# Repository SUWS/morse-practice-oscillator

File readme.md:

# Morse Code Practice oscillator

This contains the hardware and firmware designs for a morse code practice oscillator.

## Features

* 9v Battery or 12vDC powered
* Headphone or internal speaker output
* Adjustable Tone and Volume
* Support for paddle keys with variable speed and weight
* Capacitive iambic key unit included on PCB

## Sources and links

* Audio path based on designs by [Forrest Cook (WB0RIO)](http://www.solorb.com/elect/hamcirc/sidetone/)
* Capacitive Iambic key uses circuit from [John Parfrey (M0UKD)](https://m0ukd.com/homebrew/capacitive-cw-touch-key-circuits/)
* Project uses CC By icons from Dave Gandy (power icon (also remixed to make the dial and jack labels)) and Hanan (headphone icon)

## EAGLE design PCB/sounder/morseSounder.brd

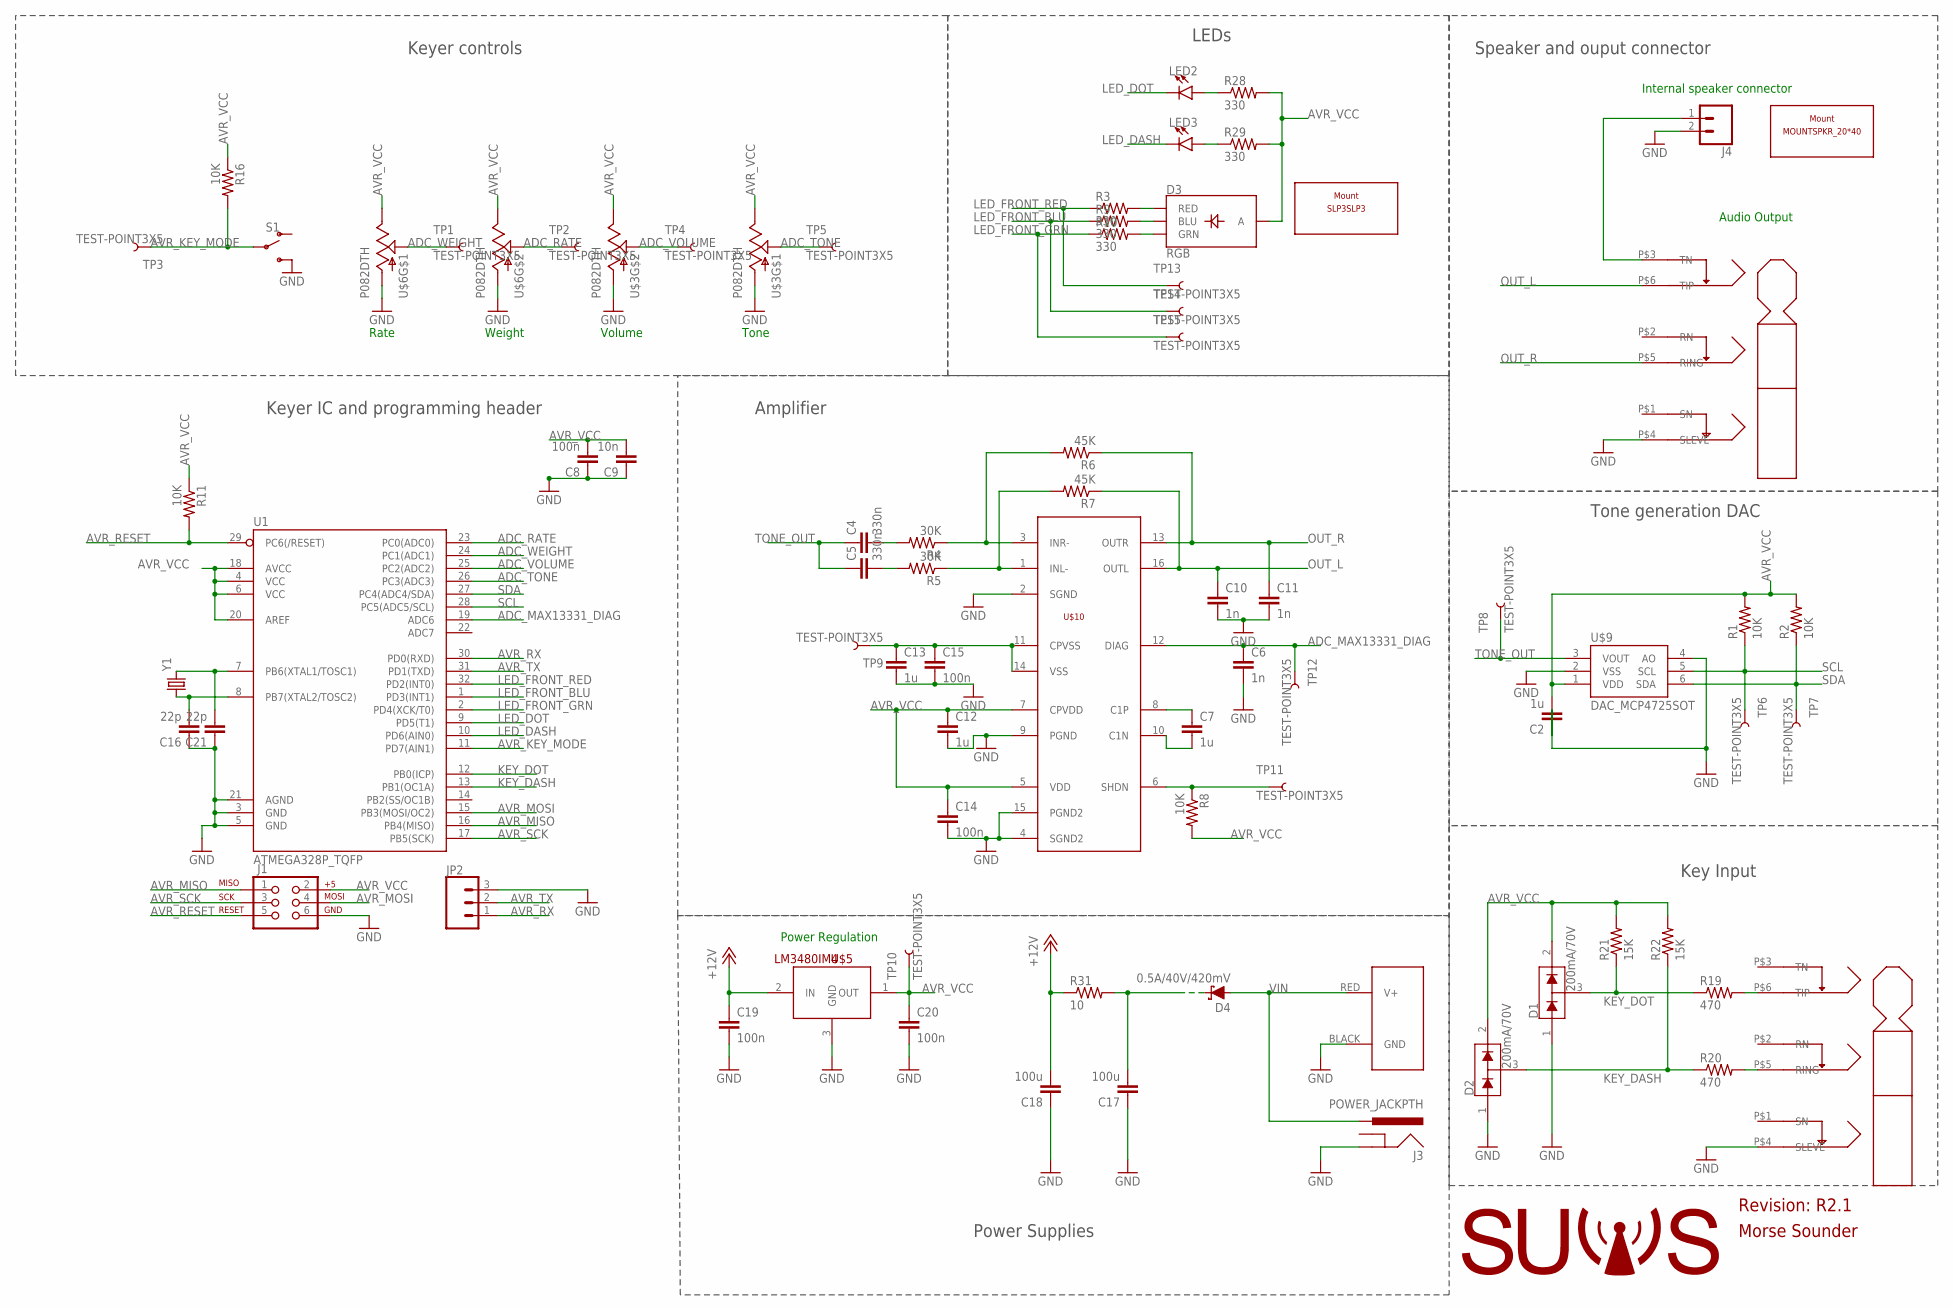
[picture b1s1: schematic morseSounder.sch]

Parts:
C2, C7, C12, C13: 1u; 0805
C4, C5: 330n; 0805
C6, C10, C11: 1n; 0805
C8, C14, C15, C19, C20: 100n; 0805
C9: 10n; 0805
C16, C21: 22p; 0805
C17, C18: 100u; 0805
D1, D2: 200mA/70V; SOT23-3
D3: RGB; P-LCC-4-3
D4: 0.5A/40V/420mV; SOD-323
J1: AVR_SPI_PRG_6PTH; 2X3
J2: POWERPOLE_POWER25A_HORIZONTAL_G2; POWERPOLE_PAIR_25A_HORIZ_G2
J3: POWER_JACKPTH; POWER_JACK_PTH
J4: CONN_02; 1X02
JP2: CONN_03; 1X03
LED2, LED3: LED-RED1206; LED-1206
R1, R2, R8, R11, R16: 10K; 0805
R3, R9, R10, R28, R29: 330; 0805
R4, R5: 30K; 0805
R6, R7: 45K; 0805
R19, R20: 470; 0805
R21, R22: 15K; 0805
R31: 10; 0805
S1: SWITCH-SPDTTE-1825232-1; TE-1825232-1
TP1, TP2, TP3, TP4, TP5, TP6, TP7, TP8, TP9, TP10, TP11, TP12, TP13, TP14, TP15: TEST-POINT3X5; PAD.03X.05
U1: ATMEGA328P_TQFP; TQFP32-08
U$1, U$2: NRJ6HH
U$3, U$6: P082DTH; P082D
U$4: MOUNTSPKR_20*40; SKR_MNT
U$5: LM3480IM4; SOT23-3
U$7: LOGO_SUWSLOGO_LARGE; LOGO_SUWS
U$8: SLP3SLP3; SLP-3
U$9: DAC_MCP4725SOT; SOT23-6
U$10: MAX13331; SSOP16
Y1: CRYSTALHC49UV; HC49U-V

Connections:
+12V: C18.2, C19.1, R31.1, U$5.2 (IN)
ADC_MAX13331_DIAG: C6.1, TP12.P$1, U1.19 (ADC6), U$10.12 (DIAG)
ADC_RATE: TP2.P$1, U1.23 (PC0(ADC0)), U$6.R2 (S)
ADC_TONE: TP5.P$1, U1.26 (PC3(ADC3)), U$3.F2 (S)
ADC_VOLUME: TP4.P$1, U1.25 (PC2(ADC2)), U$3.R2 (S)
ADC_WEIGHT: TP1.P$1, U1.24 (PC1(ADC1)), U$6.F2 (S)
AVR_KEY_MODE: R16.2, S1.2, TP3.P$1, U1.11 (PD7(AIN1))
AVR_MISO: J1.1, U1.16 (PB4(MISO))
AVR_MOSI: J1.4, U1.15 (PB3(MOSI/OC2))
AVR_RESET: J1.5, R11.2, U1.29 (PC6(/RESET))
AVR_RX: JP2.1, U1.30 (PD0(RXD))
AVR_SCK: J1.3, U1.17 (PB5(SCK))
AVR_TX: JP2.2, U1.31 (PD1(TXD))
AVR_VCC: C2.2, C8.2, C9.2, C12.1, C14.1, C20.1, D1.2 (C2), D2.2 (C2), D3.1 (A), J1.2, R1.2, R2.2, R8.2, R11.1, R16.1, R21.2, R22.2, R28.2, R29.2, TP10.P$1, U1.4 (VCC), U1.6 (VCC), U1.18 (AVCC), U1.20 (AREF), U$3.F3 (E), U$3.R3 (E), U$5.1 (OUT), U$6.F3 (E), U$6.R3 (E), U$9.1 (VDD), U$10.5 (VDD), U$10.7 (CPVDD)
GND: C2.1, C6.2, C8.1, C9.1, C10.2, C11.2, C12.2, C13.2, C14.2, C15.2, C16.1, C17.1, C18.1, C19.2, C20.2, C21.1, D1.1 (A1), D2.1 (A1), J1.6, J2.BLACK (GND), J3.GND, J4.2, JP2.3, S1.3 (S), U1.3 (GND), U1.5 (GND), U1.21 (AGND), U$1.P$4 (SLEVE), U$2.P$4 (SLEVE), U$3.F1 (A), U$3.R1 (A), U$5.3 (GND), U$6.F1 (A), U$6.R1 (A), U$9.2 (VSS), U$9.4 (AO), U$10.2 (SGND), U$10.4 (SGND2), U$10.9 (PGND), U$10.15 (PGND2)
KEY_DASH: D2.3 (COM), R20.1, R22.1, U1.13 (PB1(OC1A))
KEY_DOT: D1.3 (COM), R19.1, R21.1, U1.12 (PB0(ICP))
LED_DASH: LED3.C, U1.10 (PD6(AIN0))
LED_DOT: LED2.C, U1.9 (PD5(T1))
LED_FRONT_BLU: R9.1, TP14.P$1, U1.1 (PD3(INT1))
LED_FRONT_GRN: R10.1, TP15.P$1, U1.2 (PD4(XCK/T0))
LED_FRONT_RED: R3.1, TP13.P$1, U1.32 (PD2(INT0))
unnamed: C21.2, U1.7 (PB6(XTAL1/TOSC1)), Y1.2
unnamed: C16.2, U1.8 (PB7(XTAL2/TOSC2)), Y1.1
unnamed: D3.3 (GRN), R10.2
unnamed: C17.2, D4.C, R31.2
unnamed: C4.2, R4.2
unnamed: C5.2, R5.2
unnamed: R4.1, R6.2, U$10.3 (INR-)
unnamed: R5.1, R7.2, U$10.1 (INL-)
unnamed: R20.2, U$1.P$5 (RING)
unnamed: D3.4 (BLU), R9.2
unnamed: C7.1, U$10.8 (C1P)
unnamed: C7.2, U$10.10 (C1N)
unnamed: R19.2, U$1.P$6 (TIP)
unnamed: D3.2 (RED), R3.2
unnamed: R8.1, TP11.P$1, U$10.6 (SHDN)
unnamed: C13.1, C15.1, TP9.P$1, U$10.11 (CPVSS), U$10.14 (VSS)
unnamed: J4.1, U$2.P$3 (TN)
unnamed: LED3.A, R29.1
unnamed: LED2.A, R28.1
OUT_L: C10.1, R7.1, U$2.P$6 (TIP), U$10.16 (OUTL)
OUT_R: C11.1, R6.1, U$2.P$5 (RING), U$10.13 (OUTR)
SCL: R1.1, TP6.P$1, U1.28 (PC5(ADC5/SCL)), U$9.5 (SCL)
SDA: R2.1, TP7.P$1, U1.27 (PC4(ADC4/SDA)), U$9.6 (SDA)
TONE_OUT: C4.1, C5.1, TP8.P$1, U$9.3 (VOUT)
VIN: D4.A, J2.RED (V+), J3.PWR

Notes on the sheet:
Audio Output
Internal speaker connector
Rate
Weight
Keyer controls
Keyer IC and programming header
Power Regulation
Power Supplies
Key Input
Volume
Tone
LEDs
Tone generation DAC
Amplifier
Speaker and ouput connector
Revision: R2.1
Morse Sounder

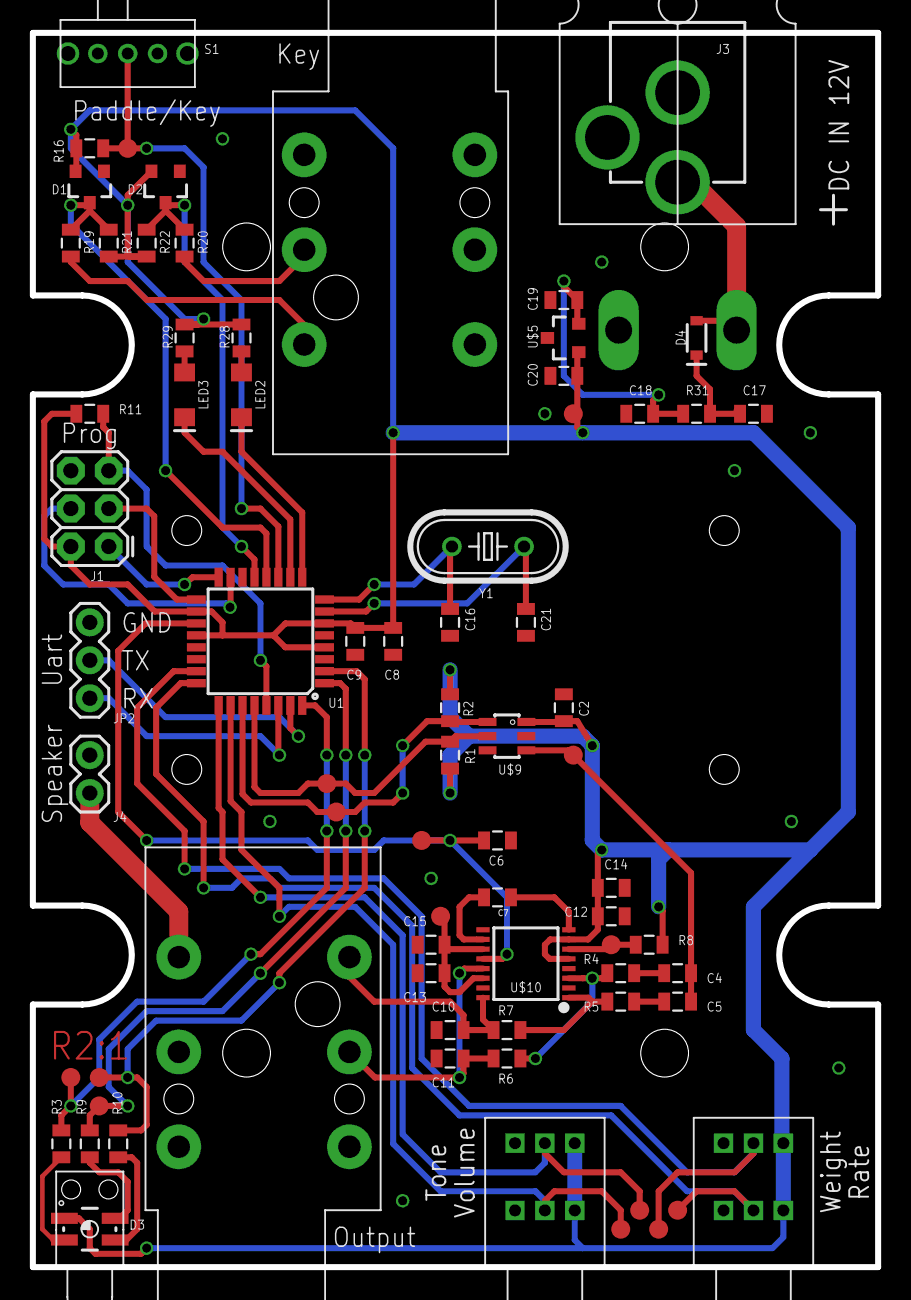
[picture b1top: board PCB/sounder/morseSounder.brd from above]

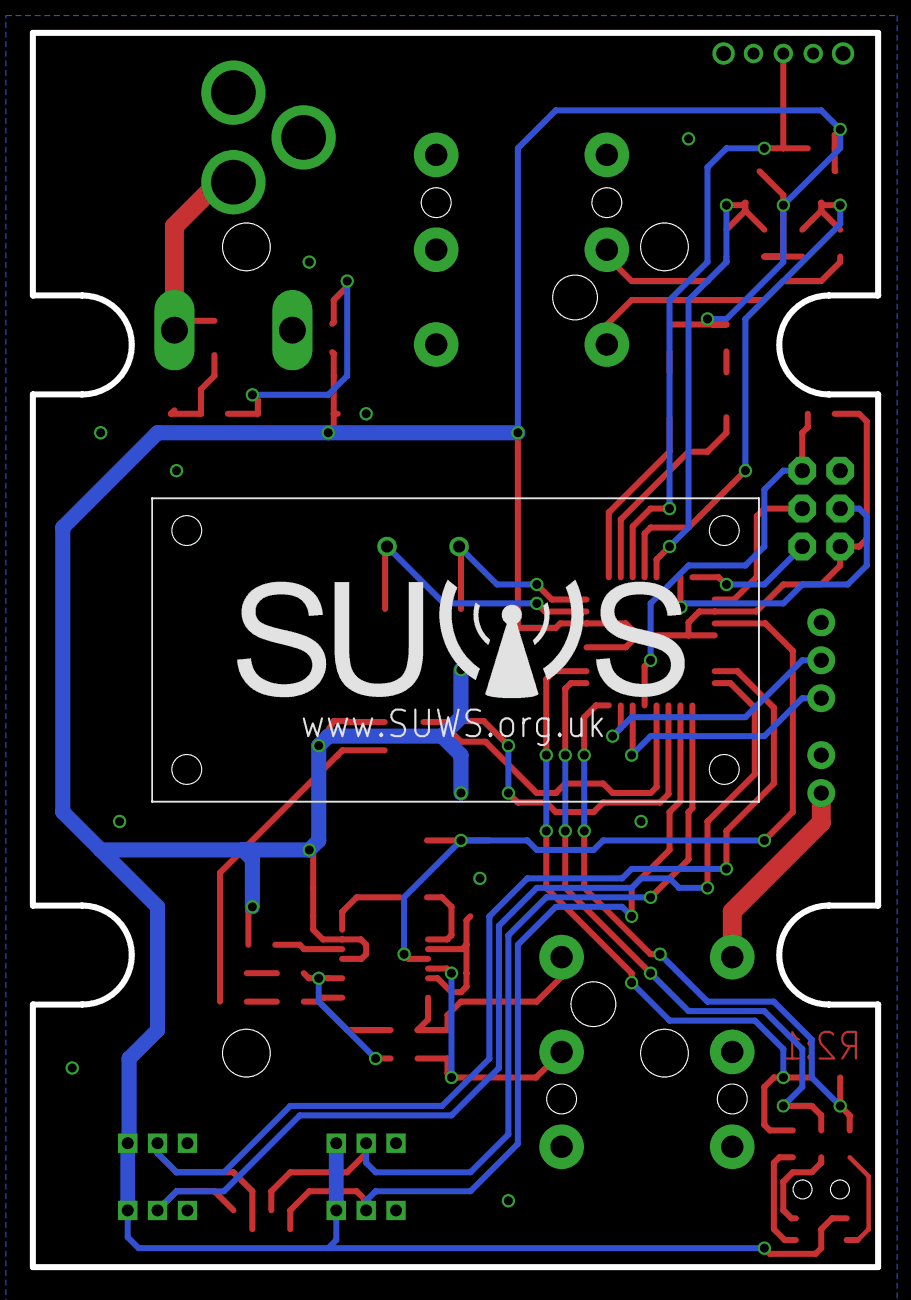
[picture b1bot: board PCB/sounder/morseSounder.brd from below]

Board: 2 copper layers, 56.6 x 82.7 mm, 77 parts (2 on the bottom side), 47 nets.

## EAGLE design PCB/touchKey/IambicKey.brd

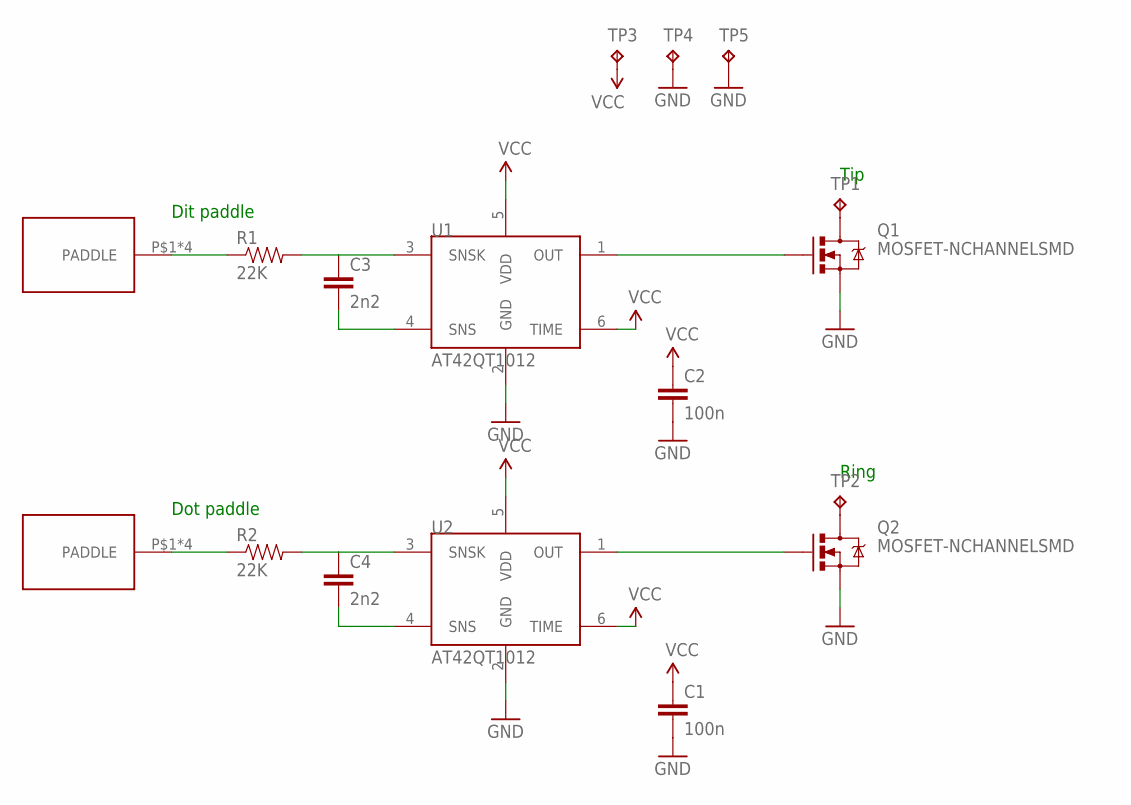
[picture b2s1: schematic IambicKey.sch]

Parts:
C1, C2: 100n; 0603-CAP
C3, C4: 2n2; 0603-CAP
Q1, Q2: MOSFET-NCHANNELSMD; SOT23-3
R1, R2: 22K; 0603-RES
TP1, TP2, TP3, TP4, TP5: TPTP20SQ; TP20SQ
U1, U2: AT42QT1012; SOT-23-6
U$1, U$2: PADDLE

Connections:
GND: C1.2, C2.2, Q1.2 (S), Q2.2 (S), TP4.TP, TP5.TP, U1.2 (GND), U2.2 (GND)
unnamed: Q1.1 (G), U1.1 (OUT)
unnamed: Q2.1 (G), U2.1 (OUT)
unnamed: C3.2, U1.4 (SNS)
unnamed: C3.1, R1.2, U1.3 (SNSK)
unnamed: R1.1, U$1.P$1, U$1.P$2, U$1.P$3, U$1.P$4
unnamed: C4.2, U2.4 (SNS)
unnamed: C4.1, R2.2, U2.3 (SNSK)
unnamed: R2.1, U$2.P$1, U$2.P$2, U$2.P$3, U$2.P$4
unnamed: Q1.3 (D), TP1.TP
unnamed: Q2.3 (D), TP2.TP
VCC: C1.1, C2.1, TP3.TP, U1.5 (VDD), U1.6 (TIME), U2.5 (VDD), U2.6 (TIME)

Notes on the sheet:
Dit paddle
Dot paddle
Tip
Ring

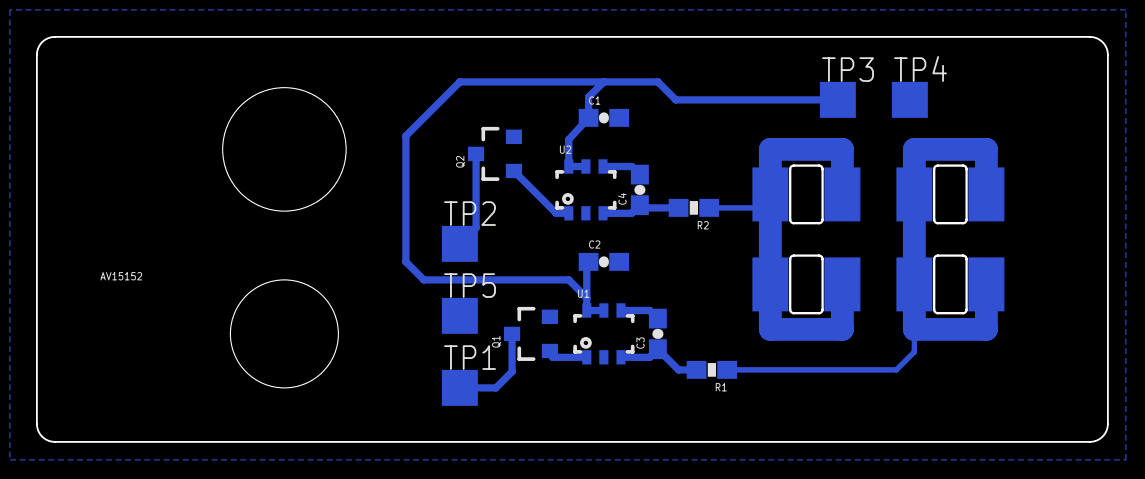
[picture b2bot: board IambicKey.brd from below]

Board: 2 copper layers, 59.5 x 22.5 mm, 17 parts (15 on the bottom side), 12 nets.

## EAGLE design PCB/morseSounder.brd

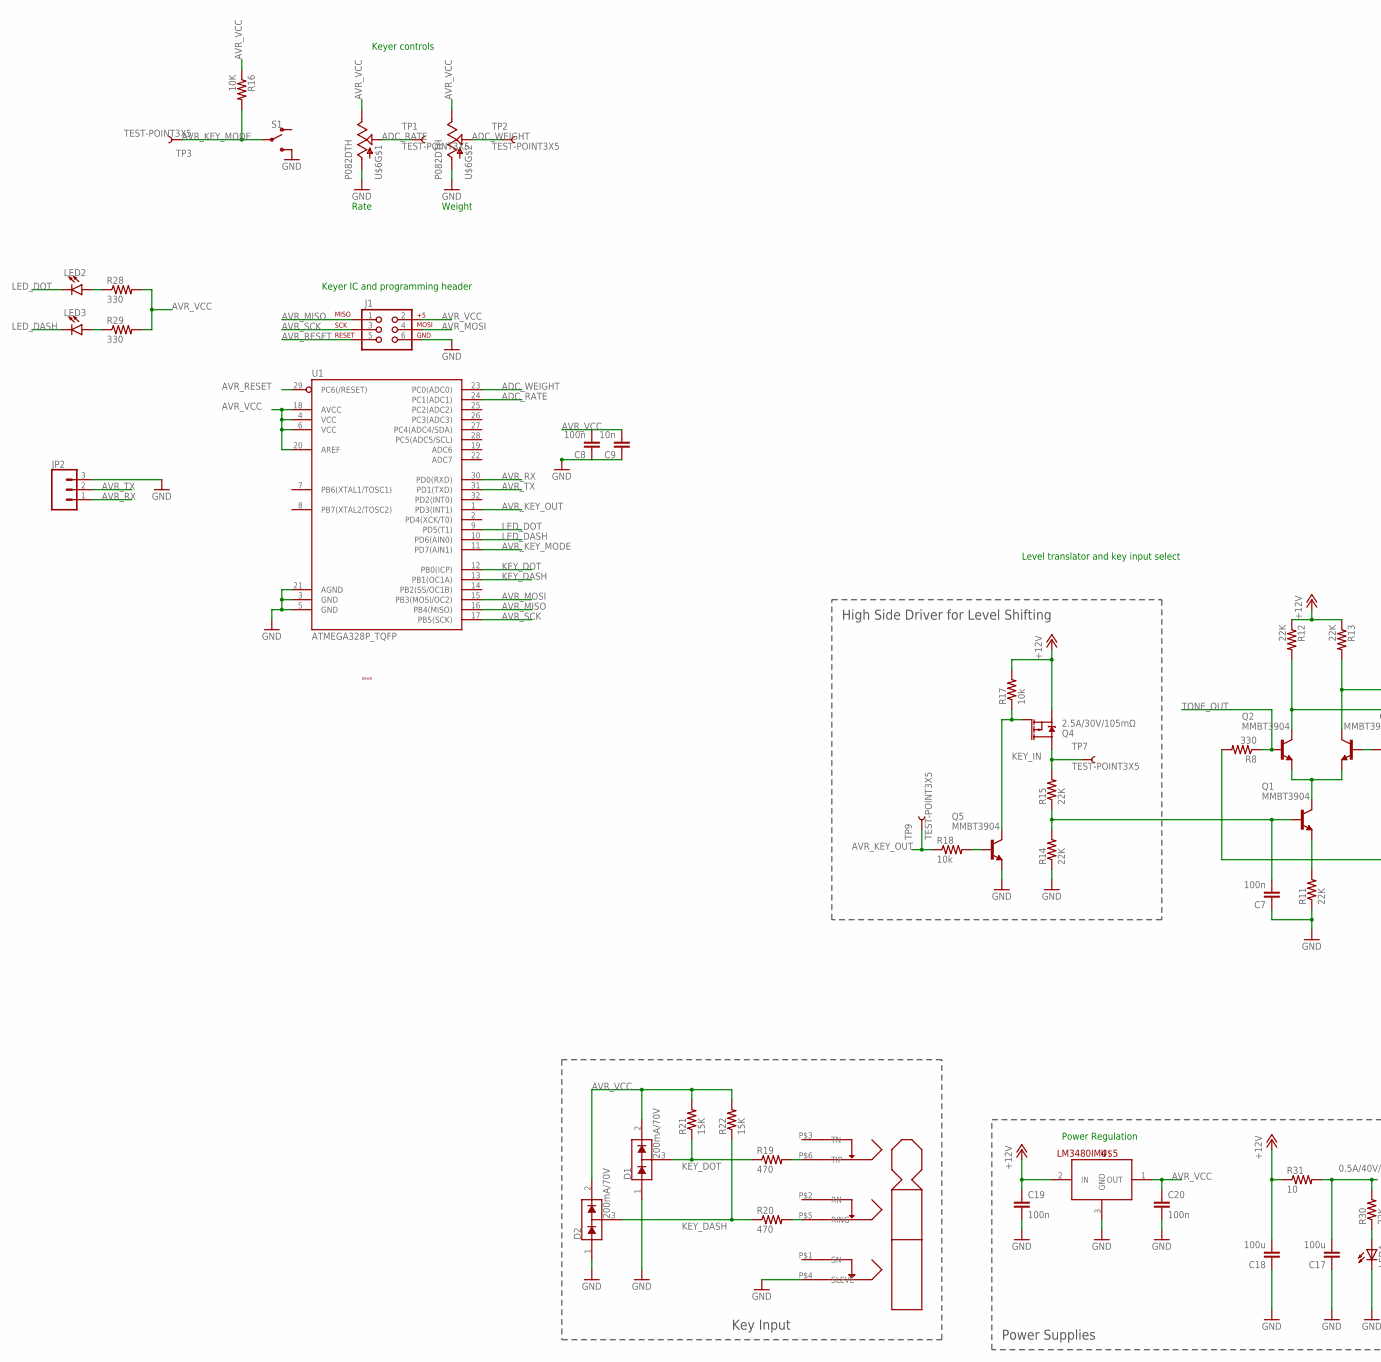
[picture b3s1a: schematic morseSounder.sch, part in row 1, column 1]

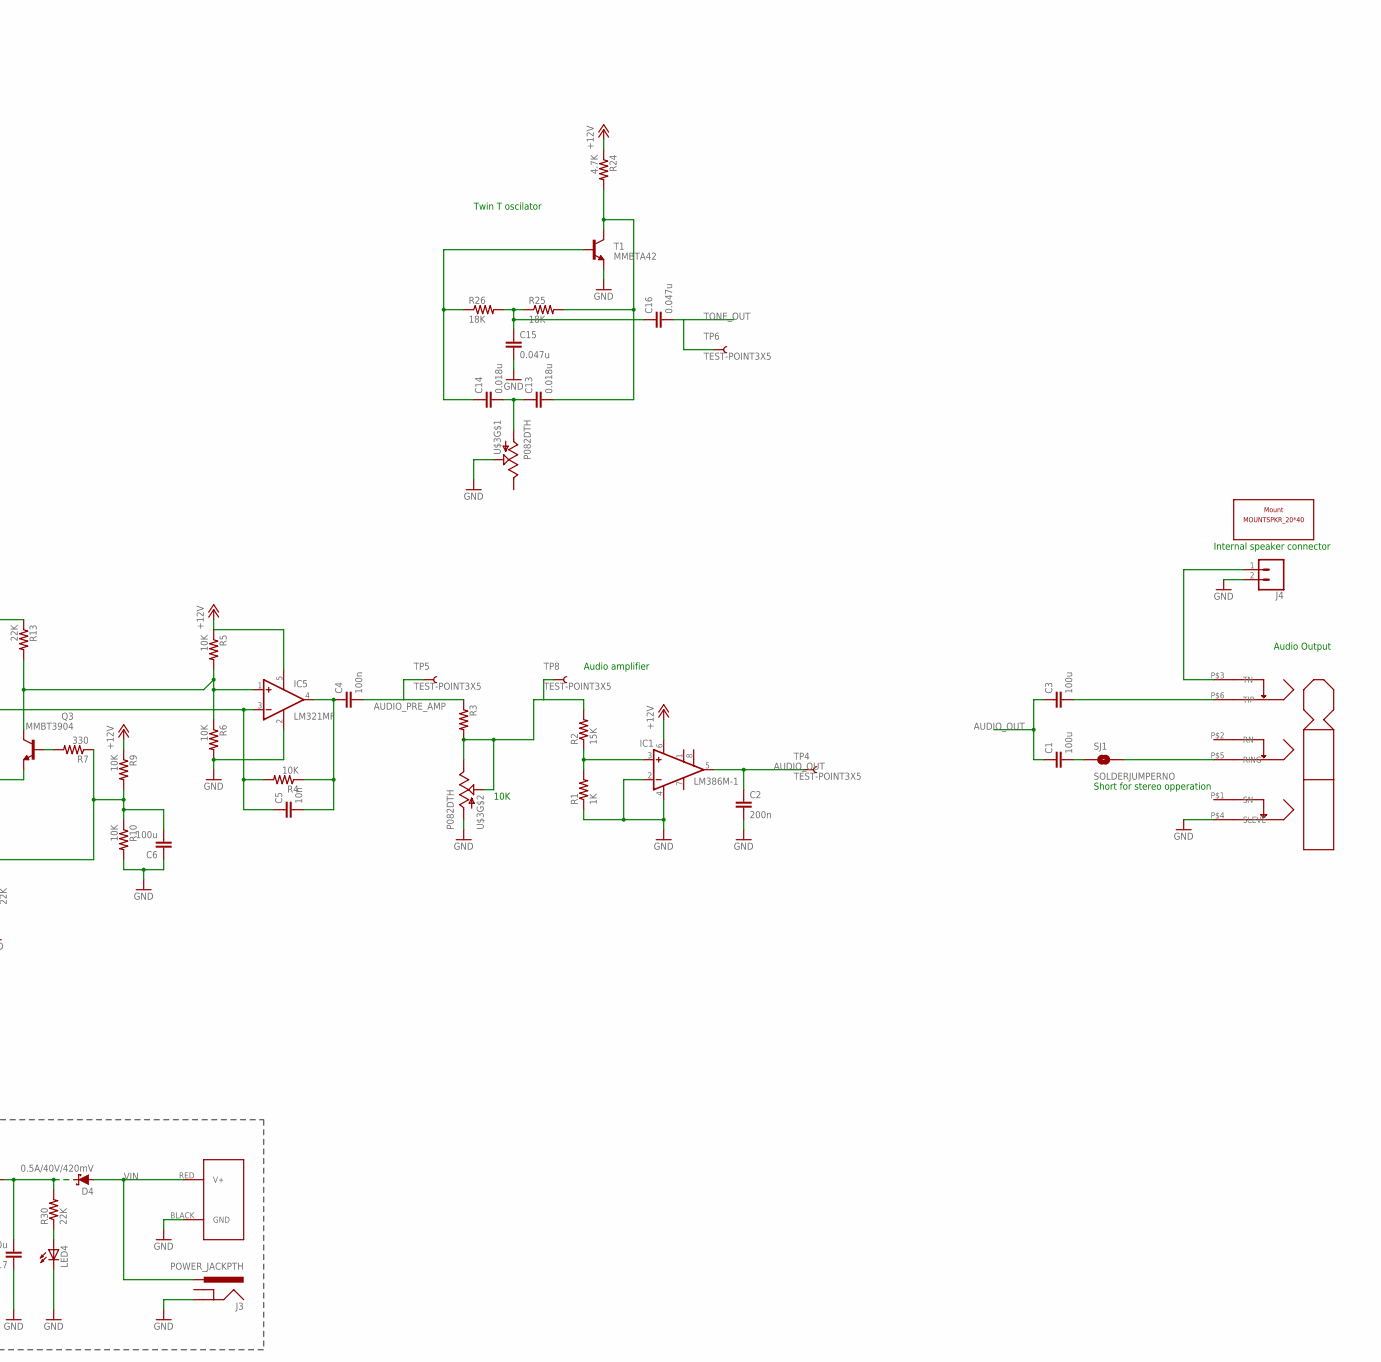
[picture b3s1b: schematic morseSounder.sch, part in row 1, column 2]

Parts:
C1, C3, C6, C17, C18: 100u; 0805
C2: 200n; 0805
C4, C7, C8, C19, C20: 100n; 0805
C5, C9: 10n; 0805
C13, C14: 0.018u; 0805
C15, C16: 0.047u; 0805
D1, D2: 200mA/70V; SOT23-3
D4: 0.5A/40V/420mV; SOD-323
IC1: LM386M-1; SO08
IC5: LM321MF; SOT23-5
J1: AVR_SPI_PRG_6PTH; 2X3
J2: POWERPOLE_POWER25A_HORIZONTAL_G2; POWERPOLE_PAIR_25A_HORIZ_G2
J3: POWER_JACKPTH; POWER_JACK_PTH
J4: CONN_02; 1X02
JP2: CONN_03; 1X03
LED2, LED3: LED-RED1206; LED-1206
LED4: LED-3MM-NO_SILK; LED3MM-NS
Q1, Q2, Q3, Q5: MMBT3904; SOT23-BEC
Q4: 2.5A/30V/105mΩ; SOT23-3
R1: 1K; 0805
R2, R21, R22: 15K; 0805
R3: RESISTOR0805-RES; 0805
R4, R5, R6, R9, R10, R16: 10K; 0805
R7, R8, R28, R29: 330; 0805
R11, R12, R13, R14, R15, R30: 22K; 0805
R17, R18: 10k; 0805
R19, R20: 470; 0805
R24: 4.7K; 0805
R25, R26: 18K; 0805
R31: 10; 0805
S1: SWITCH-SPDTTE-1825232-1; TE-1825232-1
SJ1: SOLDERJUMPERNO; SJ_2S-NO
T1: MMBTA42; SOT23
TP1, TP2, TP3, TP4, TP5, TP6, TP7, TP8, TP9: TEST-POINT3X5; PAD.03X.05
U1: ATMEGA328P_TQFP; TQFP32-08
U$1, U$2: NRJ6HH
U$3, U$6: P082DTH; P082D
U$4: MOUNTSPKR_20*40; SKR_MNT
U$5: LM3480IM4; SOT23-3
U$7: LOGO_SUWSLOGO_LARGE; LOGO_SUWS

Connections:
+12V: C18.2, C19.1, IC1.6 (VS), IC5.5 (V+), Q4.2 (S), R5.1, R9.1, R12.1, R13.1, R17.2, R24.1, R31.1, U$5.2 (IN)
ADC_RATE: TP1.P$1, U1.24 (PC1(ADC1)), U$6.F2 (S)
ADC_WEIGHT: TP2.P$1, U1.23 (PC0(ADC0)), U$6.R2 (S)
AUDIO_OUT: C1.1, C2.1, C3.1, IC1.5 (OUT), TP4.P$1
AUDIO_PRE_AMP: C4.2, R3.1, TP5.P$1
AVR_KEY_MODE: R16.2, S1.2, TP3.P$1, U1.11 (PD7(AIN1))
AVR_KEY_OUT: R18.1, TP9.P$1, U1.1 (PD3(INT1))
AVR_MISO: J1.1, U1.16 (PB4(MISO))
AVR_MOSI: J1.4, U1.15 (PB3(MOSI/OC2))
AVR_RESET: J1.5, U1.29 (PC6(/RESET))
AVR_RX: JP2.1, U1.30 (PD0(RXD))
AVR_SCK: J1.3, U1.17 (PB5(SCK))
AVR_TX: JP2.2, U1.31 (PD1(TXD))
AVR_VCC: C8.2, C9.2, C20.1, D1.2 (C2), D2.2 (C2), J1.2, R16.1, R21.2, R22.2, R28.2, R29.2, U1.4 (VCC), U1.6 (VCC), U1.18 (AVCC), U1.20 (AREF), U$5.1 (OUT), U$6.F3 (E), U$6.R3 (E)
GND: C2.2, C6.1, C7.1, C8.1, C9.1, C15.2, C17.1, C18.1, C19.2, C20.2, D1.1 (A1), D2.1 (A1), IC1.2 (-IN), IC1.4 (GND), IC5.2 (V-), J1.6, J2.BLACK (GND), J3.GND, J4.2, JP2.3, LED4.K (C), LED4.P$2, Q5.E, R1.1, R6.2, R10.2, R11.1, R14.1, S1.3 (S), T1.2 (E), U1.3 (GND), U1.5 (GND), U1.21 (AGND), U$1.P$4 (SLEVE), U$2.P$4 (SLEVE), U$3.F2 (S), U$3.R1 (A), U$5.3 (GND), U$6.F1 (A), U$6.R1 (A)
KEY_DASH: D2.3 (COM), R20.1, R22.1, U1.13 (PB1(OC1A))
KEY_DOT: D1.3 (COM), R19.1, R21.1, U1.12 (PB0(ICP))
KEY_IN: Q4.3 (D), R15.2, TP7.P$1
LED_DASH: LED3.C, U1.10 (PD6(AIN0))
LED_DOT: LED2.C, U1.9 (PD5(T1))
unnamed: C3.2, U$2.P$6 (TIP)
unnamed: C1.2, SJ1.1
unnamed: IC1.3 (+IN), R1.2, R2.1
unnamed: C17.2, D4.C, R30.2, R31.2
unnamed: C4.1, C5.2, IC5.4 (OUT), R4.1
unnamed: C5.1, IC5.3 (-IN), Q2.C, R4.2, R12.2
unnamed: IC5.1 (+IN), Q3.C, R5.2, R6.1, R13.2
unnamed: Q1.C, Q2.E, Q3.E
unnamed: C7.2, Q1.B, R14.2, R15.1
unnamed: R20.2, U$1.P$5 (RING)
unnamed: Q3.B, R7.2
unnamed: C6.2, R7.1, R8.2, R9.2, R10.1
unnamed: Q1.E, R11.2
unnamed: SJ1.2, U$2.P$5 (RING)
unnamed: R2.2, R3.2, TP8.P$1, U$3.R2 (S), U$3.R3 (E)
unnamed: Q5.B, R18.2
unnamed: Q4.1 (G), Q5.C, R17.1
unnamed: R19.2, U$1.P$6 (TIP)
unnamed: C13.2, R24.2, R25.2, T1.3 (C)
unnamed: C14.1, R26.1, T1.1 (B)
unnamed: C15.1, C16.1, R25.1, R26.2
unnamed: C13.1, C14.2, U$3.F1 (A)
unnamed: J4.1, U$2.P$3 (TN)
unnamed: LED3.A, R29.1
unnamed: LED2.A, R28.1
unnamed: LED4.A, LED4.P$1, R30.1
TONE_OUT: C16.2, Q2.B, R8.1, TP6.P$1
VIN: D4.A, J2.RED (V+), J3.PWR

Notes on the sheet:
Audio Output
10K
Audio amplifier
Twin T oscilator
Internal speaker connector
Rate
Weight
Keyer controls
Keyer IC and programming header
Level translator and key input select
Power Regulation
Short for stereo opperation
Power Supplies
Key Input
High Side Driver for Level Shifting

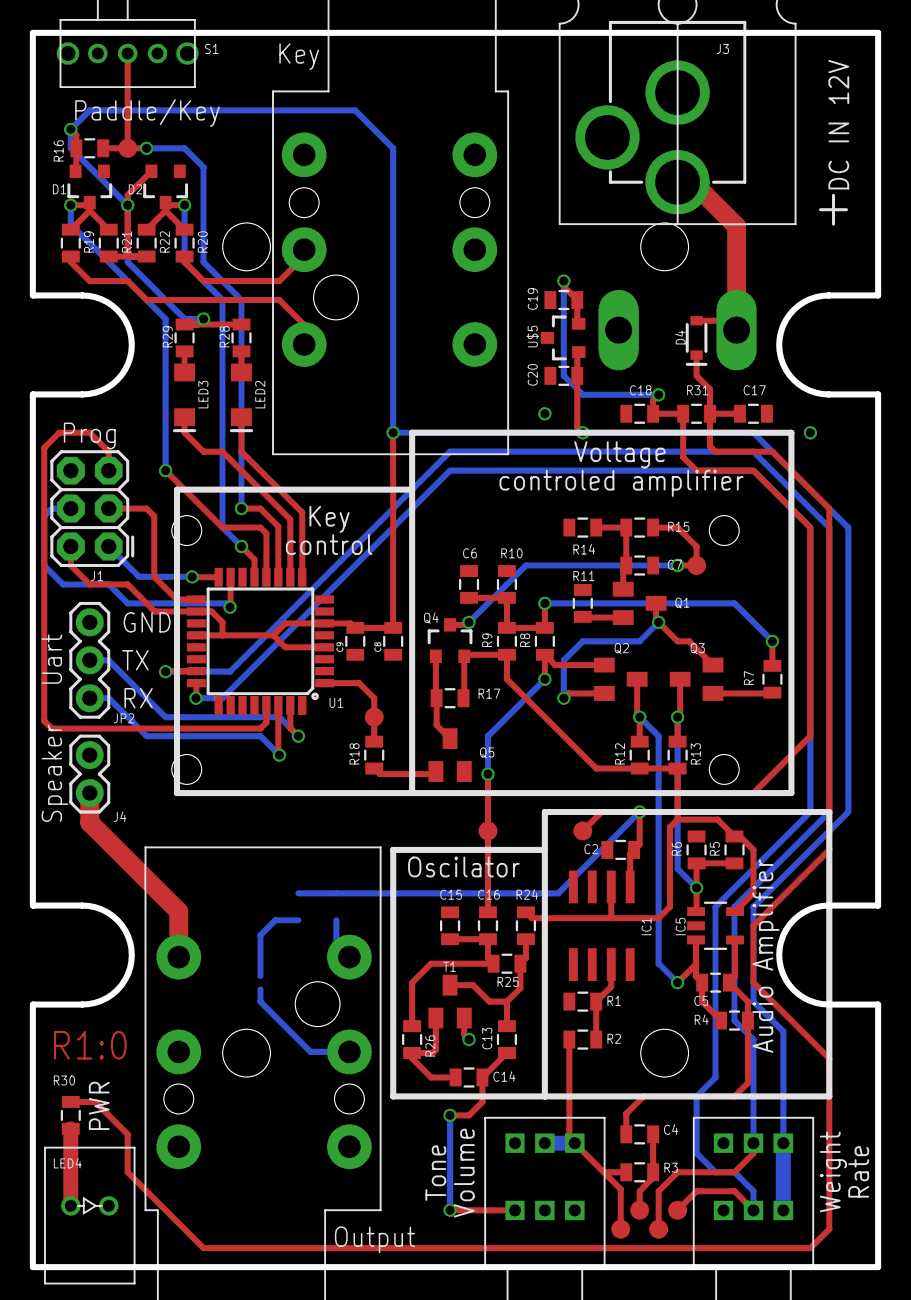
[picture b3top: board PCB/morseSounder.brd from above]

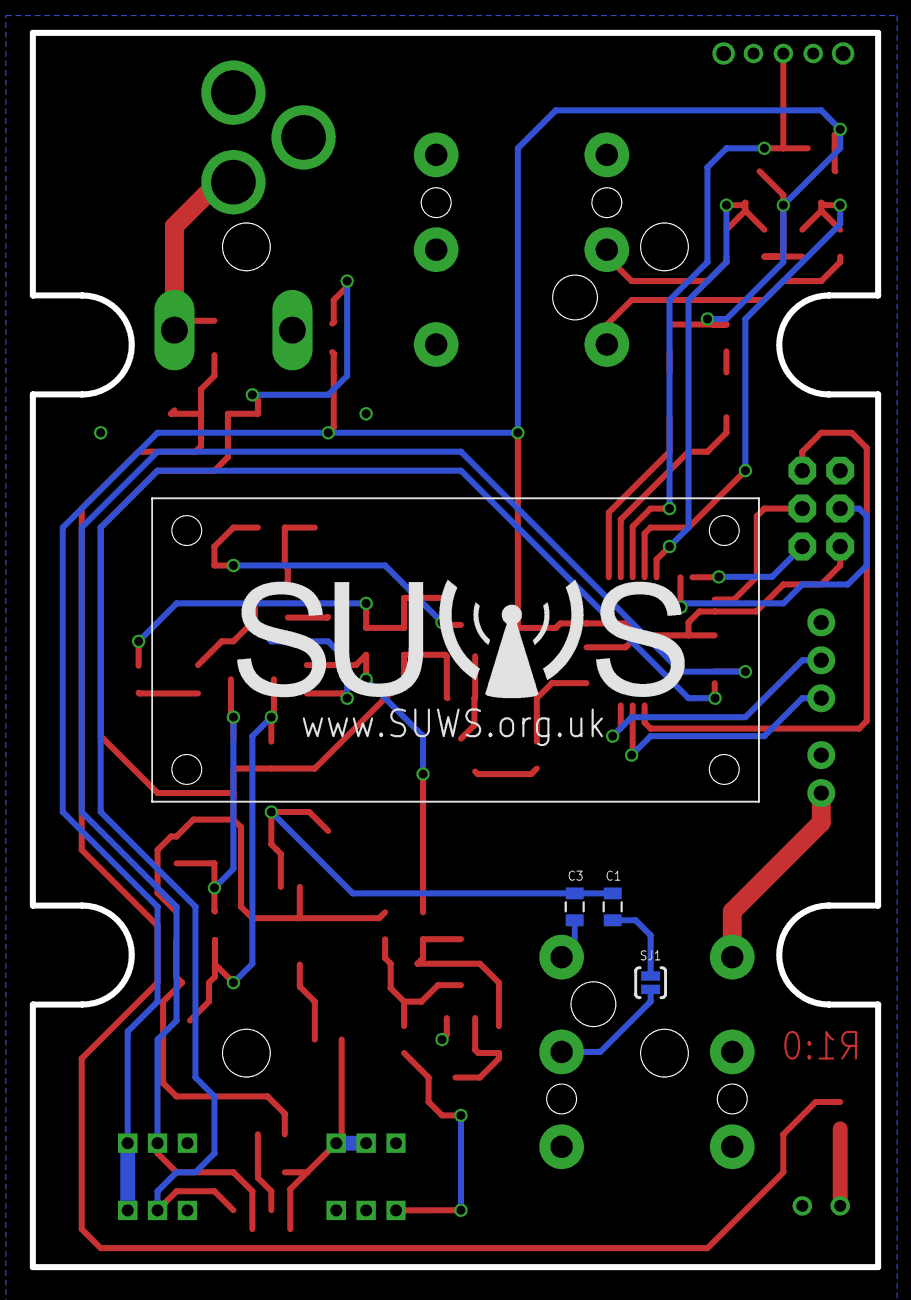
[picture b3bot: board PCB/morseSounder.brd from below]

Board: 2 copper layers, 56.6 x 82.7 mm, 84 parts (5 on the bottom side), 48 nets.

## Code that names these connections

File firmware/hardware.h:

/********************************************************************
 File Description:

 Contains pin definitions and other hardware specific options
 Hardware definitions are for r2.0 sounder hardware

********************************************************************/


#ifndef HARDWARE_H_
#define HARDWARE_H_

#define F_CPU 16000000

/* INDICATOR LED ***************************************************/

#define INDICATOR_LED_PORT PORTD  //!< port register for indicator LED
#define INDICATOR_LED_PIN PIND    //!< pin register for indicator LED
#define INDICATOR_LED_DDR DDRD    //!< data direction register for indicator led

#define INDICATOR_LED_RED PD2     //!< indicator LED red
#define INDICATOR_LED_BLUE PD3     //!< indicator LED blue
#define INDICATOR_LED_GREEN PD4     //!< indicator LED green

/* KEY INPUT *******************************************************/

#define KEY_IN_PORT PORTB         //!< port register for Key input
#define KEY_IN_PORT_PIN PINB      //!< pin register for key input
#define KEY_IN_PORT_DDR DDRB      //!< data direction register for key input

#define KEY_DOT PB0               //!< dot paddle connection also straight key input
#define KEY_STRAIGHT PB0          //!< straight key input
#define KEY_DASH PB1              //!< dash paddle connection

/* KEY INPUT LEDS **************************************************/

#define KEY_LED_PORT PORTD        //!< port register for key led indicators
#define KEY_LED_PORT_PIN PIND     //!< pin register for key led indicators
#define KEY_LED_PORT_DDR DDRD     //!< data direction register for key led indicators

#define LED_DOT PD5               //!< dot indicator LED
#define LED_DASH PD6              //!< dash indicator LED

/* SETTING INPUTS **************************************************/

#define ADC_SETTINGS_PORT PORTC   //!< port register for potentiometer input
#define ADC_SETTINGS_PORT_PIN PINC //!< pin register for potentiometer input
#define ADC_SETTINGS_PORT_DDR DDRC  //!< data direction register for potentiometer input

#define ADC_RATE PC0              //!< rate setting input
#define ADC_WEIGHT PC1            //!< weight setting input
#define ADC_VOLUME PC2            //!< weight setting input
#define ADC_TONE PC3              //!< rate setting input

#define KEY_MODE_PORT PORTD       //!< port register for key mode
#define KEY_MODE_PORT_PIN PIND    //!< pin register for key mode
#define KEY_MODE_PORT_DDR DDRD    //!< data direction register for key mode

#define KEY_MODE PD7              //!< key mode input

/* DEBUG UART INTERFACE ********************************************/

#define I2C_PORT PORTD            //!< port register for I2C
#define I2C_PIN PIND              //!< pin register for I2C
#define I2C_DDR DDRD              //!< data direction register for I2C

#define I2C_SDA PC4              //!< I2C SDA pin
#define I2C_SCL PC5              //!< I2C SCL pin

/* AMP DEBUG *******************************************************/

#define AMP_DEBUG_PORT PORTC      //!< port register for amplifier debug
#define AMP_DEBUG_PIN PINC        //!< pin register for amplifier debug
#define AMP_DEBUG_DDR DDRC        //!< data direction register for amplifier debug

#define AMP_DEBUG PC6             //!< amplifier debug input

/* DEBUG UART INTERFACE ********************************************/

#define DEBUG_UART_PORT PORTD     //!< port register for debug uart
#define DEBUG_UART_PORT_PIN PIND  //!< pin register for debug uart
#define DEBUG_UART_PORT_DDR DDRD  //!< data direction register for debug uart

#define DEBUG_TX PD1              //!< debug uart transmit pin
#define DEBUG_RX PD0              //!< debug uart receive pin

#endif /* HARDWARE_H_ */

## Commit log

2016-05-29 Added initial schematic and ltspice simulations
2016-05-29 Added gitignore and readme
2016-05-30 Added avr based keyer and key input stages
2016-05-30 Added power supply circuitry
2016-06-17 Added Touch keyer circuit and initial board
2016-12-24 optimized schematic components and added initial board file
2017-02-09 Replaced most through hole components with SMD equivilents
2017-02-16 Tidied up silk screen on PCB
2017-02-19 Added test points and cleaned up some silkscreen issues
2017-02-21 * Removed the pair of unused opto-isolators. * Commenced tidying up the schematic. & Removal of 3rd opto-isolator may prove tricky...
2017-02-22 Add files via upload
    This is the firmware embedded c code running on the avr chip, still havnt done the key_mode configuration yet will do soon and still need to do a final check if the other pin features have been met o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
2017-02-23 * Removed opto-isolator driving the amplifier. Swapped to a high side MOSFET driver. Note this makes the micro mandatory. * Added input protection for the key.
2017-02-23 * Oops! Power reverse protection diode should protect both power inputs!
2017-02-25 Routed rest of PCB
    Altered pin placement on AVR
    Added additional protection to key input
    Separated LEDS from key input
2017-02-25 Added some decoupling capacitors and tidied silk screen
2017-03-05 Swapped power LED for right angle version
2017-03-05 moved PCB files
2017-03-05 Moved touch key PCB files
2017-03-05 Created PCB sub gitignore and removed PCB ignores from main gitignore
2017-03-05 Added initial case panel designs
2017-03-05 Added back panel with jack power option
2017-03-05 Added panellised R1:0 PCBs
2017-03-11 Refined designs for PCB order
2017-03-11 Updated readme with external sources and confirmed features
2017-03-23 Made pin chages to the firmware code
    and changed the adc read function a bit
    - still need to verify it by tyler
    - still need to test the code using a test circuit on my ilmatto (need
    to discuss it with tyler)
    - Need to implement adc keymode
2017-03-25 Added licence document
2017-03-25 Moved firmware to separate folder
    Moved hardware definitions to separate file
2017-03-27 Added makefile and travis build file
2018-03-26 Rebuilt audio circuit to use a synthesised digital source rather than a tone generator.
    Other improvements.
    RGB power light/status indicator.
    Better amplifier circuit.
2018-03-26 Modified front panel for new light pipe design
2018-03-26 Merged new board and front panel onto single panel for manufacture
2018-04-30 Added hardware.h for r2.0
    Also replaced main function with basic test program.
2018-05-01 Updated makefile for chip used on board
2018-05-01 Added more test code to test the ADC and digital inputs.
    Also added basic uart printing for debug output.
2018-05-03 Added basic test of DAC and audio output path
2018-05-05 Moved uart code to its own file
2018-05-05 moved ADC code out of main file
2018-05-05 Moved MCP4625 and i2c code to seperate files
2018-05-05 Added a tone generator function which creates the required tones.
    Also added a file for LED control and moved the I2c writing code for the
    MCP4725 to the I2C file.
2018-05-05 Added variable output tone to tone generator
2018-05-05 fixed compiler errors and warnings
2018-05-05 Moved I2C to an interrupt based system.
2018-05-06 moved tone generation code out of testing function
2018-05-06 Tone generation is now entireley interrupt driven
2018-05-06 Moved tone triggering code from ToneTest and into the main function.
    Also added function documentaion to the tone Generator
2018-05-07 Added basic iambic keying functionality
2018-05-07 Added code to continualty update settings from the dials
2018-05-07 fix first dash being sent as a dot
2018-09-23 Added mechanical design files for sounder
2018-09-23 Added mechanical deisgn files for key
2018-09-23 Fixed Pinout of DAC chip
2018-09-23 Added document frame to the Sounder Schematic
2018-09-29 bumped version number on boards and updated panel 1 with new design
2018-09-29 Fixed mode switch being back to front
2018-09-29 Fixed bug with partial first dot in iambic mode
2018-10-02 Moved wave to seperate files ready fro move to PROGMEM
2018-10-02 Wave now fetched by function rather than extern table
2018-10-02 sine wave now moved to program memory
2018-10-02 Implemented volume control.
2018-10-03 Fixed compiler warnings
2019-03-18 Added red led indication on tone
2022-07-25 Flip weight and rate controls to match front pannel
2022-07-25 Move test code to a seperate program
2022-07-25 Move power LED control to main file
2022-07-25 Update component values to reduce volume and remove output distortion
2022-07-25 Ensure ADC returns to zero after tone output
    Also adjust volume curve to provide more low volume options.

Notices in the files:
parts and their libraries:
SparkFun: Licensing: CC v3.0 Share-Alike You are welcome to use this library for commercial purposes.
SparkFun-PowerIC: Licensing: Creative Commons ShareAlike 4.0 International - https://creativecommons.org/licenses/by-sa/4.0
